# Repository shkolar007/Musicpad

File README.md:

# Musicpad

This is a macropad to control music playing on your computer.

It features 4 keys with underglow, a rotary encoder, an OLED display, and a cool Claude Code logo on the case!

I built this macropad for [Hackpad](https://hackpad.hackclub.com/)—an awesome Hack Club YSWS project run by [Alex Ren](https://github.com/qcoral).

- 4 keys
- EC11 rotary encoder
- 128x32 OLED Display
- Cool underglow

## CAD
To assemble it, you will need:
  - 3x M3 bolts for the case (required)
  - 3x M3 heat inserts for the case (required)
  - 4x M3 bolts and nuts to secure the PCB into the case (optional)

*Made in Fusion 360*

## PCB
Fully designed in KiCad!

<--- schematic

<--- PCB

## Firmware Features

  ### 1st Layer (Base Features)
  - Key 1 - Play/Pause
  - Key 2 - Prev track
  - Key 3 - Next track
  - Key 4 - Mute
  - Encoder press - Mute
  - Encoder turn - Volume Up/Down

  ### 2nd Layer (While Encoder is Held)
  - Key 1 - RGB Toggle
  - Key 2 - RGB Mode
  - Key 3 - Hue -
  - Key 4 - Hue +
  - Encoder press - Bootloader
  - Encoder turn - Brightness Up/Down

*Note: Key 1/2/3/4 correspond to SW 1/2/3/4 on the PCB.*

## BOM

| Quantity | Component | Status |
| :---: | :--- | :--- |
| 1x | Seeed XIAO RP2040 | Must have |
| 1x | 0.91-inch OLED display | Must have |
| 1x | EC11 Rotary encoder | Must have |
| 6x | SK6812 MINI-E LEDs | Must have |
| 4x | Cherry MX Switches | Must have |
| 4x | DSA keycaps | Must have |
| 3x | M3x5x4mm heat-set inserts | Must have |
| 3x | M3x16mm screws | Must have |
| 3x | 3D printed case parts | Must have |
| 1x | Musicpad PCB | Must have |
| 1x | 3D printed Claude Code logo | Must have |
| 4x | M3x8mm screws | Optional |
| 4x | M3 nuts | Optional |

## Assembly

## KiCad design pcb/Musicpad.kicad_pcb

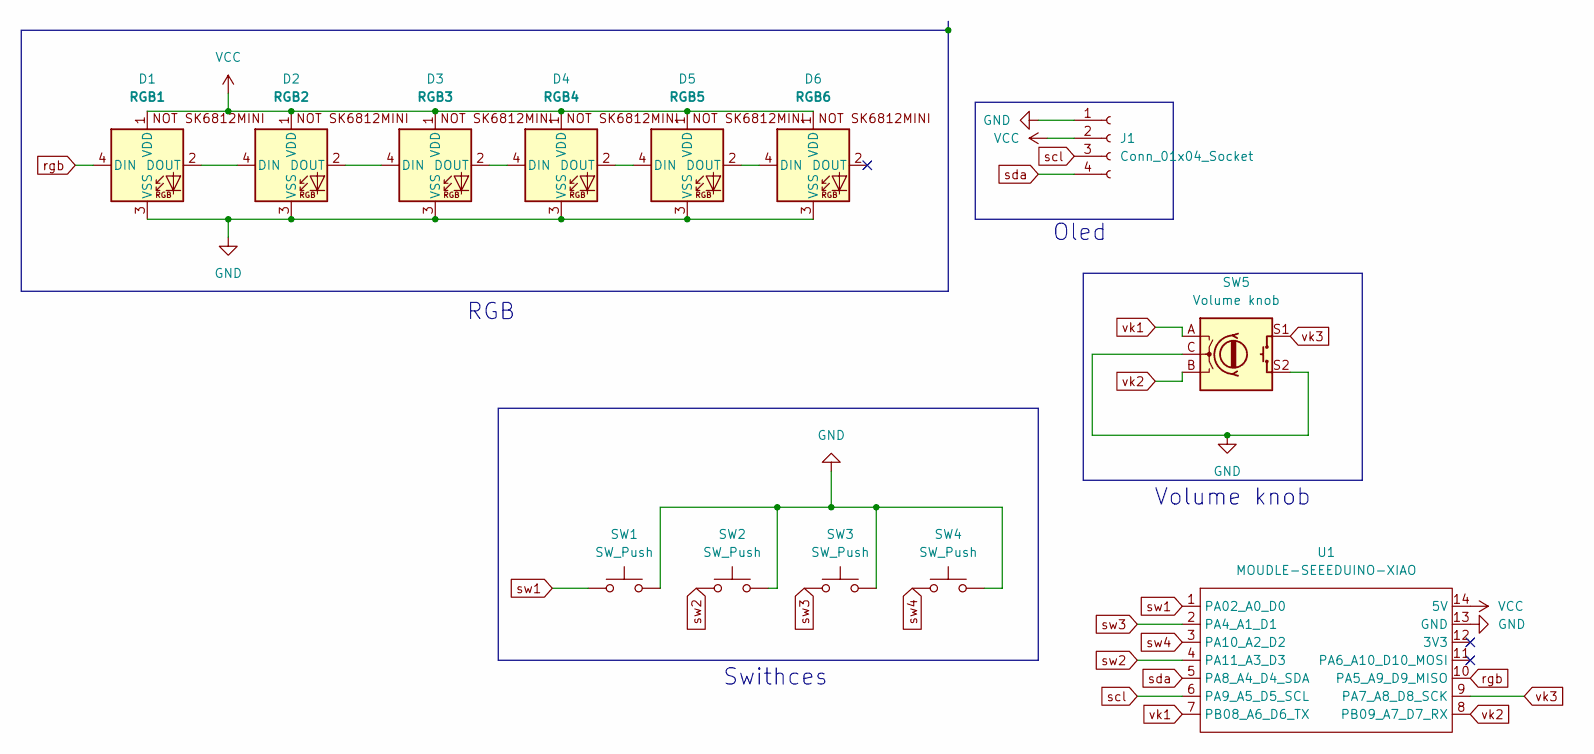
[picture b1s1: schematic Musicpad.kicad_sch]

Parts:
D1: RGB1; SK6812MINI-E_fixed
D2: RGB2; SK6812MINI-E_fixed
D3: RGB3; SK6812MINI-E_fixed
D4: RGB4; SK6812MINI-E_fixed
D5: RGB5; SK6812MINI-E_fixed
D6: RGB6; SK6812MINI-E_fixed
J1: Conn_01x04_Socket; PinSocket_1x04_P2.54mm_Vertical
SW1, SW2, SW3, SW4: SW_Push; SW_Cherry_MX_1.00u_PCB
SW5: Volume knob; RotaryEncoder_Alps_EC11E-Switch_Vertical_H20mm
U1: MOUDLE-SEEEDUINO-XIAO; XIAO-Generic-Hybrid-14P-2.54-21X17.8MM

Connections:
GND: D1.3 (VSS), D2.3 (VSS), D3.3 (VSS), D4.3 (VSS), D5.3 (VSS), D6.3 (VSS), J1.1, SW1.2, SW2.2, SW3.2, SW4.2, SW5.C, SW5.S2, U1.13 (GND)
unnamed: D1.2 (DOUT), D2.4 (DIN)
unnamed: D2.2 (DOUT), D3.4 (DIN)
unnamed: D3.2 (DOUT), D4.4 (DIN)
unnamed: D4.2 (DOUT), D5.4 (DIN)
unnamed: D5.2 (DOUT), D6.4 (DIN)
VCC: D1.1 (VDD), D2.1 (VDD), D3.1 (VDD), D4.1 (VDD), D5.1 (VDD), D6.1 (VDD), J1.2, U1.14 (5V)
rgb: D1.4 (DIN), U1.10 (PA5_A9_D9_MISO)
scl: J1.3, U1.6 (PA9_A5_D5_SCL)
sda: J1.4, U1.5 (PA8_A4_D4_SDA)
sw1: SW1.1, U1.1 (PA02_A0_D0)
sw2: SW2.1, U1.4 (PA11_A3_D3)
sw3: SW3.1, U1.2 (PA4_A1_D1)
sw4: SW4.1, U1.3 (PA10_A2_D2)
vk1: SW5.A, U1.7 (PB08_A6_D6_TX)
vk2: SW5.B, U1.8 (PB09_A7_D7_RX)
vk3: SW5.S1, U1.9 (PA7_A8_D8_SCK)

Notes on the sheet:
Volume knob
Oled
RGB
Swithces

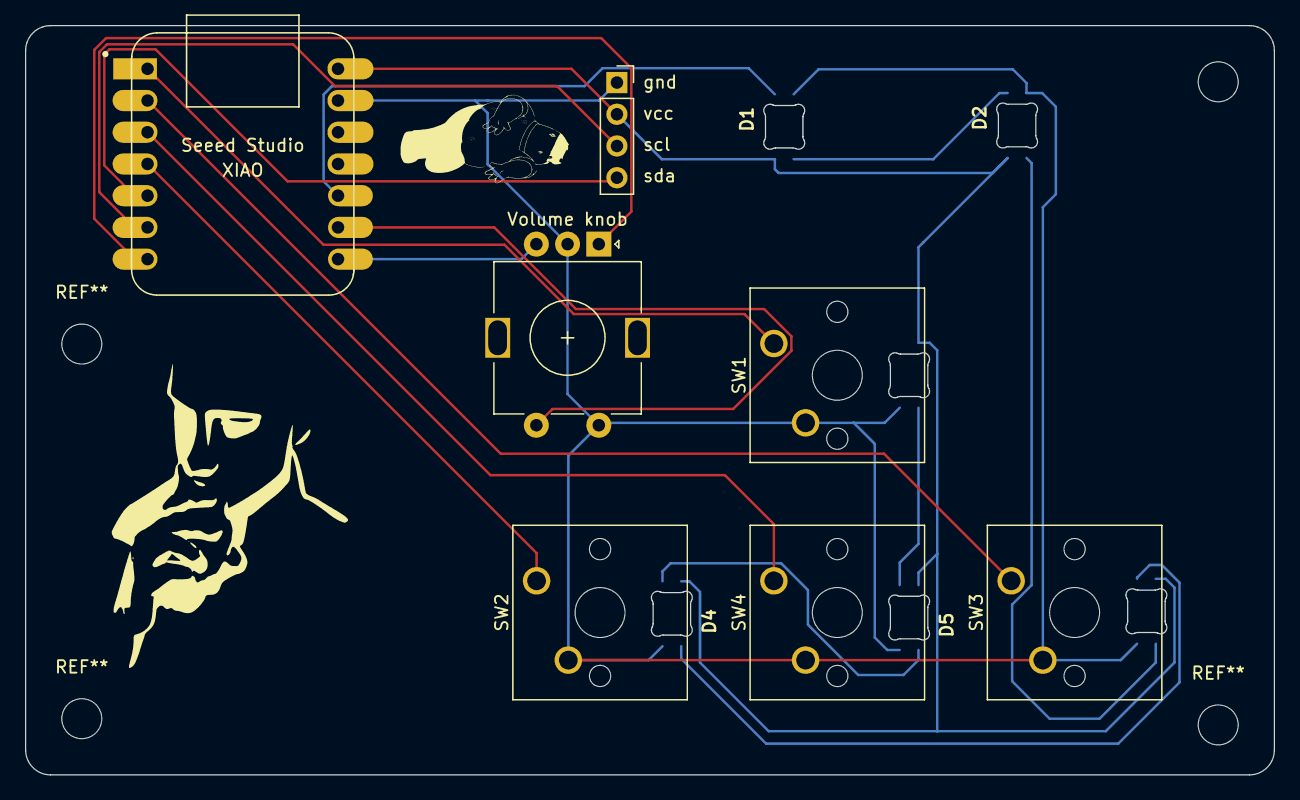
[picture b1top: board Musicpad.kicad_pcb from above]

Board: 2 copper layers, 100.0 x 60.0 mm, 13 parts (0 on the bottom side), 17 nets.
